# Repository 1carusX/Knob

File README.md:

# Knob — 车机蓝牙旋钮配件

> 目标车机的「蓝牙物理旋钮配件」DIY 项目。
>
> **硬件端**：ESP32-S3 + 圆形屏 + 旋转编码器，通过自定义 BLE GATT 服务上报单击/双击/长按事件（转动只在旋钮本地生效），同时接收车况显示数据，并支持经蓝牙升级固件（OTA）。
> **车机端**：Android App（壳 + DEX 热加载插件），解析旋钮事件并翻译成车控动作（空调 / 座椅通风加热），同时把车况回显给旋钮屏幕。

## 核心思路

```mermaid
flowchart LR
    HW["硬件配件<br/>ESP32-S3 + 编码器 + 圆形屏"]
    subgraph CAR["车机"]
        SHELL["壳 App<br/>车机厂商签名，只签一次"]
        DEX["plugin.dex<br/>全部车控/业务逻辑，可热更新"]
        SHELL -- DexClassLoader --> DEX
    end
    HW <-- "自定义 BLE GATT<br/>双向：事件 / 回显 / 固件 OTA" --> DEX
```

- **硬件 = 旋钮**，不知道也不关心自己在控制什么，只管上报事件、显示手机推来的数据。
- **App = 大脑**，负责事件→动作映射，执行车控，并把结果回显给旋钮屏幕。
- **壳只签名一次**，只负责加载插件、日志和权限申请；BLE 连接、车控、界面全在插件里，后续所有代码更新通过下发插件完成，避免反复"上传→签名→装车"。
- **插件包顺带升级旋钮**：插件和旋钮固件打成一个 zip 分发，插件连上旋钮发现固件版本不一样就自动 OTA，旋钮装在车上不用再拆下来插电脑。

（最初计划走标准 BLE HID 键盘 + 无障碍服务捕获按键，实测目标车机没有暴露无障碍服务开关入口、这条路走不通，现已替换为上面这套自定义 GATT 方案，详见 `docs/项目历程与架构.md`。）

## 目录结构

```
├── app/                 # 壳 App（Android 工程，cn.icarus.knob）
│   ├── 使用与验证指南.md  # App 用法 / 实车验证步骤说明书
│   └── app/src/
│       ├── byd/ · generic/  # 按平台分的 flavor：权限声明 + PlatformConfig
│       └── main/java/cn/icarus/knob/
│           ├── api/          # 壳↔DEX 契约：KnobPlugin / KnobHost / Ui
│           ├── plugin/       # PluginLoader：导入并加载 plugin.dex
│           ├── host/         # KnobHostImpl：壳向插件提供的能力（只剩日志）
│           ├── util/         # 日志（LogSink）/ CrashHandler
│           └── KnobActivity / KnobApp / BootReceiver / RuntimePerm
├── plugin/               # 插件工程（编译产出 output/plugin.dex，可反复更新）
│   └── src/main/
│       ├── flags-real/ · flags-simulate/  # BuildFlags.kt：真实车控 / 模拟两个变体
│       └── kotlin/cn/icarus/knob/
│           ├── api/               # 与壳完全相同的契约副本（改动须两边同步）
│           └── plugin/
│               ├── MainPlugin.kt      # KnobPlugin 接口实现（入口 + 停靠点状态机 + 页面路由）
│               ├── page/              # 触屏页面，一个页面一个文件
│               ├── CarCommands.kt     # onCommand / onQuery 命令清单
│               ├── CarActions.kt      # 停靠点的车控读写（空调、座椅）
│               ├── CarPermissions.kt  # 车控运行时权限（只在用户点按钮时申请）
│               ├── StartupCheck.kt    # 启动自检（通过才连旋钮）
│               ├── KnobOta.kt         # 旋钮固件自动升级
│               ├── DriveFeed.kt       # 旋钮驾驶页的数据源
│               ├── BleManager.kt      # 自定义 BLE GATT：扫描配对、重连、按键/显示编解码、固件 OTA
│               ├── FirmwareBundle.kt  # 从插件包里读出并校验旋钮固件
│               ├── CarControl.kt      # 车控引擎（BYDAUTO 调用）
│               └── PluginSelfTest.kt  # 一键全量自检
├── firmware/             # 旋钮固件（PlatformIO，ESP32-S3+GC9A01+EC11，含自定义 BLE GATT 通信和 OTA）
│   └── simulate/         # 电脑上用真 LVGL 渲染屏幕截图/动画（CMake），改界面不用烧板子
├── hardware/             # 旋钮 PCB（KiCad）：V1 / V2
├── store/                # 应用商店素材（图标 + 预览图）
└── docs/                 # 全部分析知识 / 方案
    ├── INDEX.md          # ← 文档索引（先读这个）
    ├── 项目历程与架构.md   # 完整发展历程 + 当前架构/协议/交互设计
    ├── 验证结论.md        # 实车验证事实清单（持续更新）
    ├── 设计/旋钮圆屏UI/    # 圆屏界面设计稿（PNG/HTML + 规格），由 gen.mjs 生成
    └── ROADMAP.md        # 路线图与当前状态
```

## 快速开始

```bash
# 壳 App（比亚迪车机）→ app/app/build/outputs/apk/bydRelease/app-byd-release-unsigned.apk
cd app && ./gradlew assembleBydRelease

# 插件包（插件 + 旋钮固件）→ plugin/output/knob-plugin-<板子>-<固件版本>.zip
# 板子：Pcb（V1）/ PcbV2 / Devkit；需要 PlatformIO（pio）
cd plugin && ./gradlew pluginPackagePcb

# 只要插件、不带固件 → plugin/output/plugin.dex（SDK 版本见根目录 gradle/libs.versions.toml，SDK 路径自动探测）
cd plugin && ./gradlew pluginDex
```

装车流程：U 盘安装壳 APK（需车机厂商签名版）→ 打开壳点「📥 选择插件」，用文件选择器选中插件包 zip 或 `plugin.dex`（自动拷进 App 私有目录，之后每次启动自动加载）→ 右半边出现插件页面即成功。导入的是插件包时，插件连上旋钮会自动给旋钮升级固件。更多构建变体（`generic` 壳、模拟版插件）见 `AGENTS.md` §4，装车细节见 `app/使用与验证指南.md`。

## 关键事实（已验证）

- 无 root、无 adb，只能 U 盘装 APK。
- `BYDAUTO_AC_GET/SET`、`BYDAUTO_SETTING_GET/SET` 是 **signature 级权限**（protectionLevel=2），普通签名 App 车机不授予 → 直接 HAL 车控被挡死（实测，见 `docs/验证结论.md`）。
- 能直接控车的应用都持有车机厂商签发的签名，且不存在额外的包名白名单——拿到签名即获得对应权限。本项目已通过官方开发者认证流程申请到车机厂商签名，只用官方 SDK 声明的接口（未声明的方法通过反射调用，见 `docs/项目历程与架构.md`）。
- 无障碍服务方案已弃用：最初计划用无障碍服务捕获蓝牙 HID 按键，实测目标车机没有暴露无障碍服务开关入口，无法启用，已替换为自定义 BLE GATT 双向通道，无障碍服务在本项目中不再使用。

## 文档导航

所有知识文档的索引见 [`docs/INDEX.md`](docs/INDEX.md)；工具/代理请先读 [`AGENTS.md`](AGENTS.md)。

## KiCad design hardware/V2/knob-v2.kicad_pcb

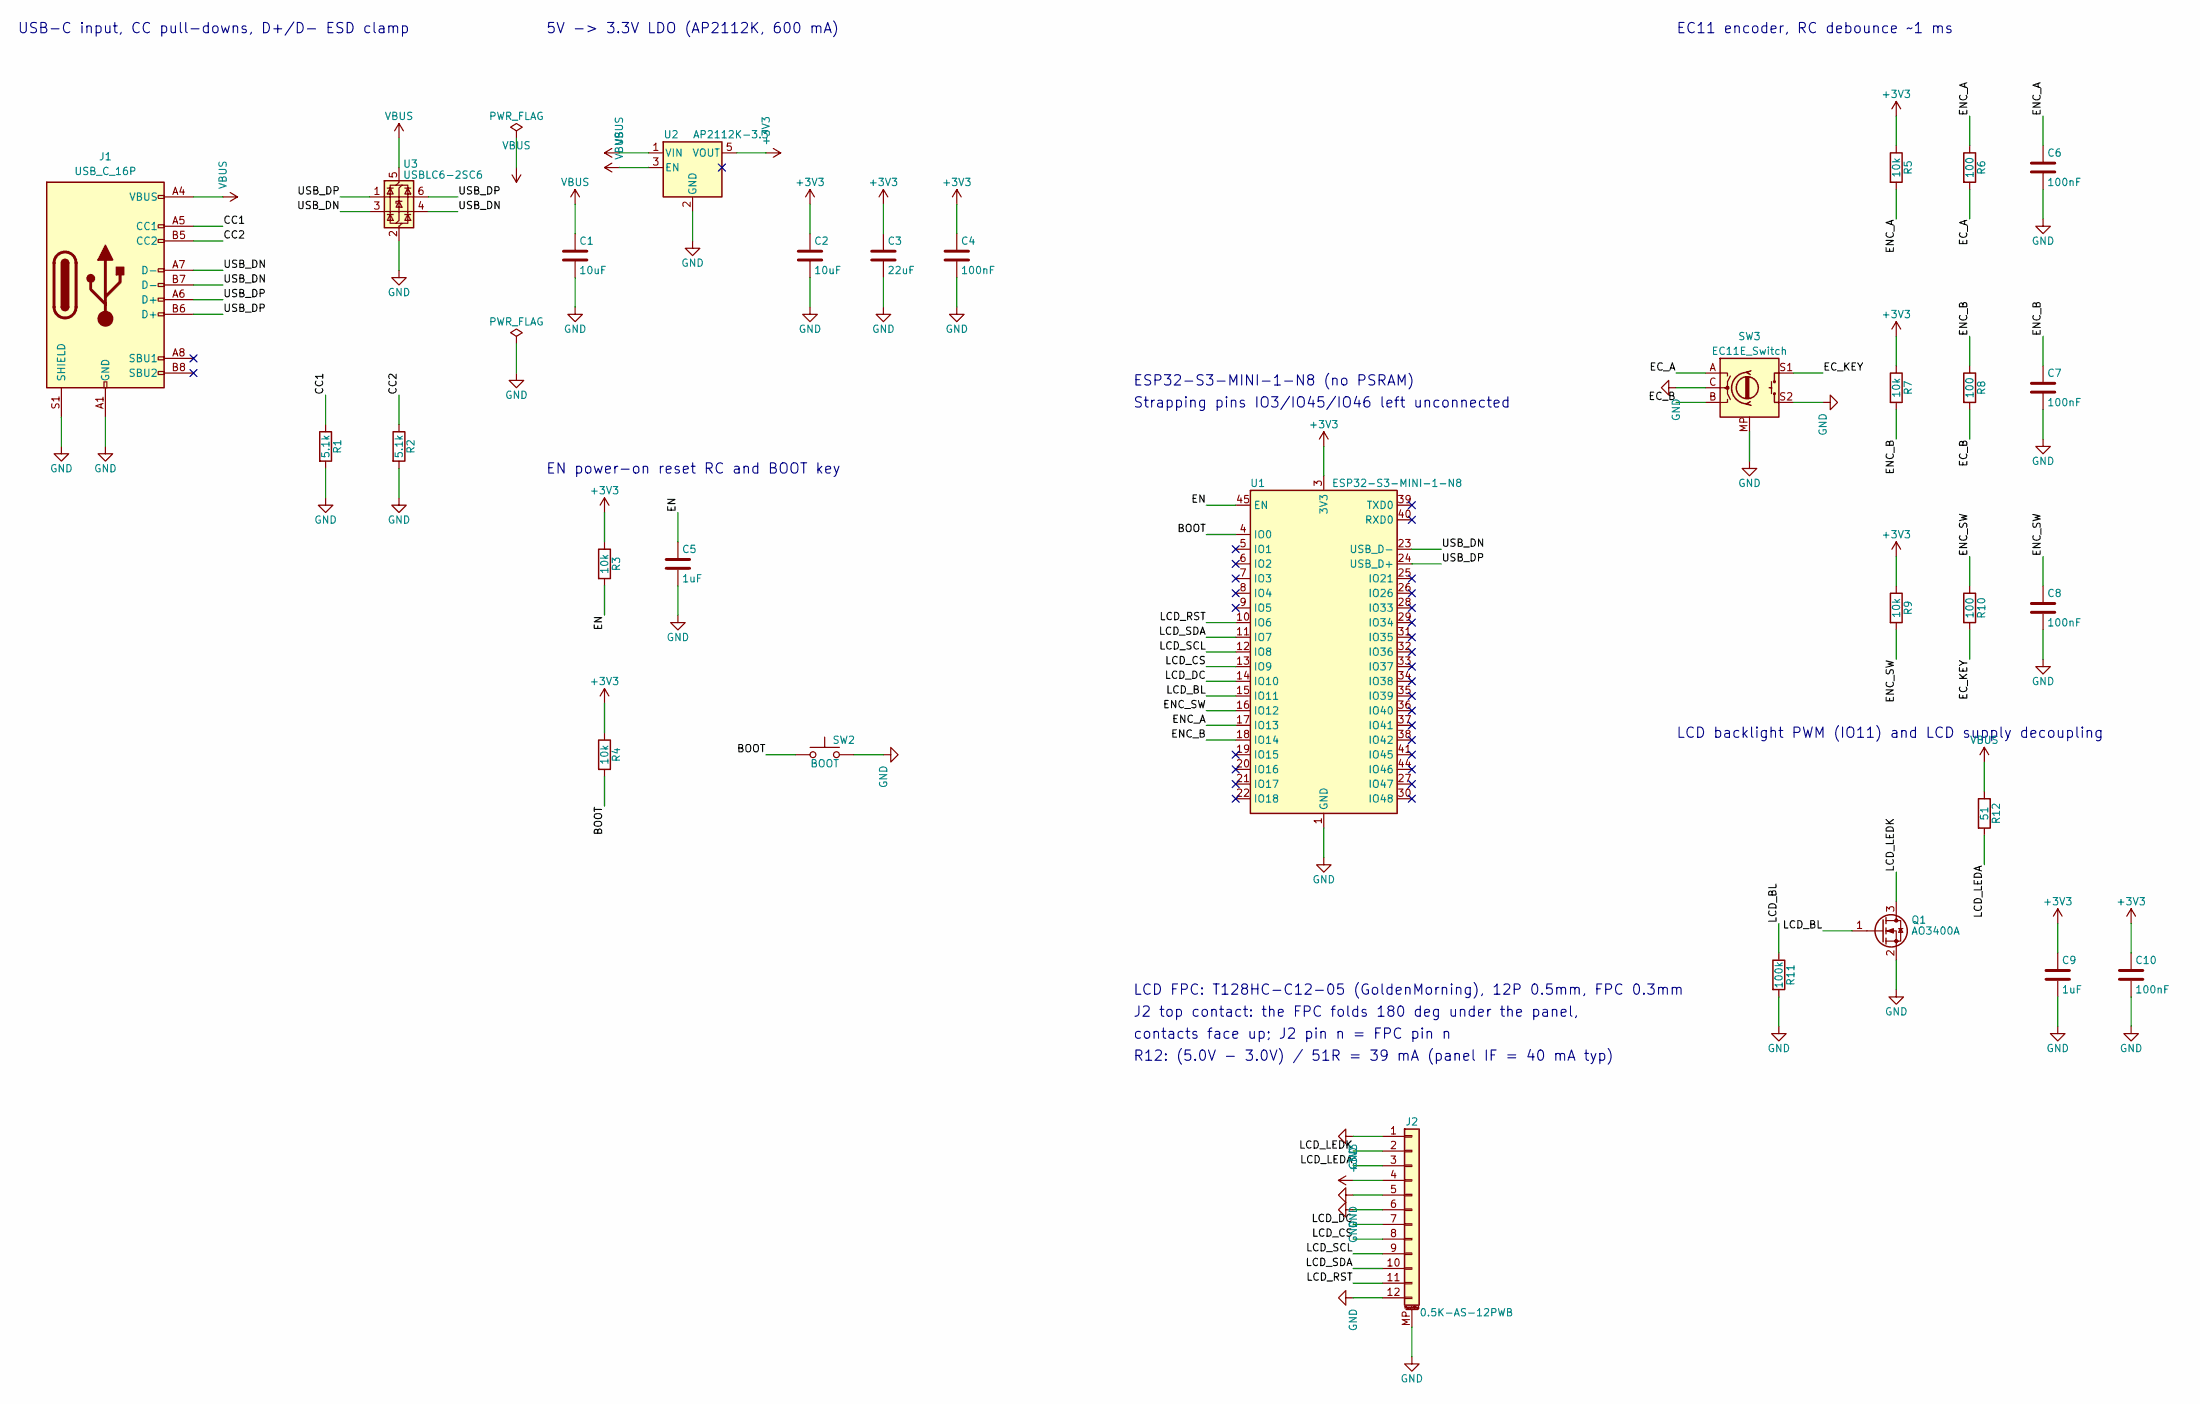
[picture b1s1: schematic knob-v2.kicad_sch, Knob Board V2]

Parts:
C1, C2: 10uF; C_0603_1608Metric
C3: 22uF; C_0805_2012Metric
C4, C6, C7, C8, C10: 100nF; C_0402_1005Metric
C5, C9: 1uF; C_0402_1005Metric
J1: USB_C_16P; USB_C_Receptacle_HRO_TYPE-C-31-M-12
J2: 0.5K-AS-12PWB; FPC_HDGC_0.5K-AS-12PWB_1x12-1MP_P0.50mm_Horizontal
Q1: AO3400A; SOT-23
R1, R2: 5.1k; R_0402_1005Metric
R3, R4, R5, R7, R9: 10k; R_0402_1005Metric
R6, R8, R10: 100; R_0402_1005Metric
R11: 100k; R_0402_1005Metric
R12: 51; R_0805_2012Metric
SW2: BOOT; SW_Alps_SKRTLAE010_Keepout
SW3: EC11E_Switch; RotaryEncoder_EC11C01V01-0027_Switch_Vertical
U1: ESP32-S3-MINI-1-N8; ESP32-S2-MINI-1
U2: AP2112K-3.3; SOT-23-5
U3: USBLC6-2SC6; SOT-23-6

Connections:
+3V3: C2.1, C3.1, C4.1, C9.1, C10.1, J2.4, R3.1, R4.1, R5.1, R7.1, R9.1, U1.3 (3V3), U2.5 (VOUT)
/BOOT: R4.2, SW2.1, U1.4 (IO0)
/CC1: J1.A5 (CC1), R1.1
/CC2: J1.B5 (CC2), R2.1
/EC_A: R6.2, SW3.A
/EC_B: R8.2, SW3.B
/EC_KEY: R10.2, SW3.S1
/EN: C5.1, R3.2, U1.45 (EN)
/ENC_A: C6.1, R5.2, R6.1, U1.17 (IO13)
/ENC_B: C7.1, R7.2, R8.1, U1.18 (IO14)
/ENC_SW: C8.1, R9.2, R10.1, U1.16 (IO12)
/LCD_BL: Q1.1 (G), R11.1, U1.15 (IO11)
/LCD_CS: J2.8, U1.13 (IO9)
/LCD_DC: J2.7, U1.14 (IO10)
/LCD_LEDA: J2.3, R12.2
/LCD_LEDK: J2.2, Q1.3 (D)
/LCD_RST: J2.11, U1.10 (IO6)
/LCD_SCL: J2.9, U1.12 (IO8)
/LCD_SDA: J2.10, U1.11 (IO7)
/USB_DN: J1.A7 (D-), J1.B7 (D-), U1.23 (USB_D-), U3.3 (I/O2), U3.4 (I/O2)
/USB_DP: J1.A6 (D+), J1.B6 (D+), U1.24 (USB_D+), U3.1 (I/O1), U3.6 (I/O1)
GND: C1.2, C2.2, C3.2, C4.2, C5.2, C6.2, C7.2, C8.2, C9.2, C10.2, J1.A1 (GND), J1.A12 (GND), J1.B1 (GND), J1.B12 (GND), J1.S1 (SHIELD), J2.1, J2.5, J2.6, J2.12, J2.MP (MountPin), Q1.2 (S), R1.2, R2.2, R11.2, SW2.2, SW3.C, SW3.MP, SW3.S2, U1.1 (GND), U1.2 (GND), U1.42 (GND), U1.43 (GND), U1.46 (GND), U1.47 (GND), U1.48 (GND), U1.49 (GND), U1.50 (GND), U1.51 (GND), U1.52 (GND), U1.53 (GND), U1.54 (GND), U1.55 (GND), U1.56 (GND), U1.57 (GND), U1.58 (GND), U1.59 (GND), U1.60 (GND), U1.61 (GND), U1.62 (GND), U1.63 (GND), U1.64 (GND), U1.65 (GND), U2.2 (GND), U3.2 (GND)
VBUS: C1.1, J1.A4 (VBUS), J1.A9 (VBUS), J1.B4 (VBUS), J1.B9 (VBUS), R12.1, U2.1 (VIN), U2.3 (EN), U3.5 (VBUS)

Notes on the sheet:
USB-C input, CC pull-downs, D+/D- ESD clamp
5V -> 3.3V LDO (AP2112K, 600 mA)
EN power-on reset RC and BOOT key
ESP32-S3-MINI-1-N8 (no PSRAM)
Strapping pins IO3/IO45/IO46 left unconnected
EC11 encoder, RC debounce ~1 ms
LCD backlight PWM (IO11) and LCD supply decoupling
LCD FPC: T128HC-C12-05 (GoldenMorning), 12P 0.5mm, FPC 0.3mm
J2 top contact: the FPC folds 180 deg under the panel,
contacts face up; J2 pin n = FPC pin n
R12: (5.0V - 3.0V) / 51R = 39 mA (panel IF = 40 mA typ)

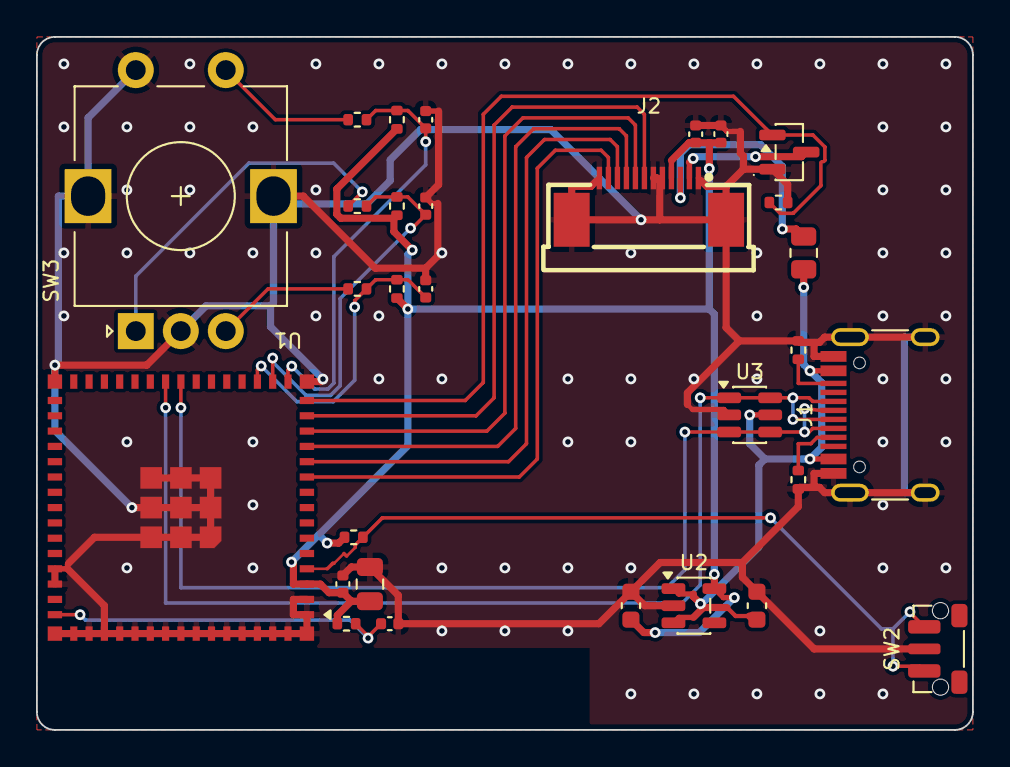
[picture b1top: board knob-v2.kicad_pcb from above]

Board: 2 copper layers, 52.0 x 38.5 mm, 30 parts (0 on the bottom side), 23 nets.

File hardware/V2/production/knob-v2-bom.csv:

Comment,Designator,Footprint,JLCPCB Part #
10uF,"C1,C2",0603,C19702
100nF,"C4,C6,C7,C8,C10",0402,C1525
22uF,C3,0805,C45783
1uF,"C5,C9",0402,C52923
USB_C_16P,J1,SMD,C165948
0.5K-AS-12PWB,J2,"SMD,P=0.5mm",C2911755
AO3400A,Q1,SOT-23,C20917
5.1k,"R1,R2",0402,C25905
100,"R6,R8,R10",0402,C25076
100k,R11,0402,C25741
51,R12,0805,C17738
10k,"R3,R4,R5,R7,R9",0402,C25744
BOOT,SW2,"SMD,4.5x3.4mm",C110293
AP2112K-3.3,U2,SOT-25-5,C51118
USBLC6-2SC6,U3,SOT-23-6L,C7519
